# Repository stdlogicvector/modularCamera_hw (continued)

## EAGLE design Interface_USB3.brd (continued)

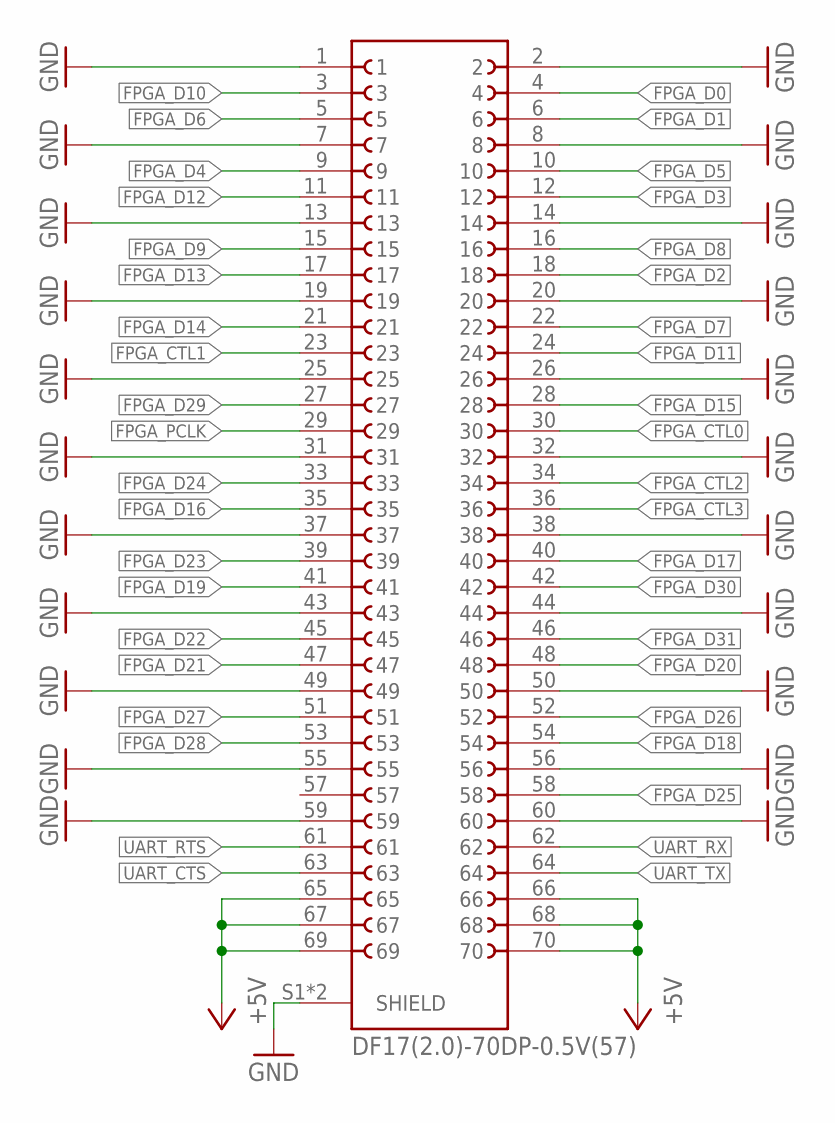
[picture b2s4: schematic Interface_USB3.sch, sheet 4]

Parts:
J1: DF17(2.0)-70DP-0.5V(57)

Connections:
+5V: J1.65, J1.66, J1.67, J1.68, J1.69, J1.70; also elsewhere on the board
FPGA_CTL0: J1.30; also elsewhere on the board
FPGA_CTL1: J1.23; also elsewhere on the board
FPGA_CTL2: J1.34; also elsewhere on the board
FPGA_CTL3: J1.36; also elsewhere on the board
FPGA_D0: J1.4; also elsewhere on the board
FPGA_D1: J1.6; also elsewhere on the board
FPGA_D2: J1.18; also elsewhere on the board
FPGA_D3: J1.12; also elsewhere on the board
FPGA_D4: J1.9; also elsewhere on the board
FPGA_D5: J1.10; also elsewhere on the board
FPGA_D6: J1.5; also elsewhere on the board
FPGA_D7: J1.22; also elsewhere on the board
FPGA_D8: J1.16; also elsewhere on the board
FPGA_D9: J1.15; also elsewhere on the board
FPGA_D10: J1.3; also elsewhere on the board
FPGA_D11: J1.24; also elsewhere on the board
FPGA_D12: J1.11; also elsewhere on the board
FPGA_D13: J1.17; also elsewhere on the board
FPGA_D14: J1.21; also elsewhere on the board
FPGA_D15: J1.28; also elsewhere on the board
FPGA_D16: J1.35; also elsewhere on the board
FPGA_D17: J1.40; also elsewhere on the board
FPGA_D18: J1.54; also elsewhere on the board
FPGA_D19: J1.41; also elsewhere on the board
FPGA_D20: J1.48; also elsewhere on the board
FPGA_D21: J1.47; also elsewhere on the board
FPGA_D22: J1.45; also elsewhere on the board
FPGA_D23: J1.39; also elsewhere on the board
FPGA_D24: J1.33; also elsewhere on the board
FPGA_D25: J1.58; also elsewhere on the board
FPGA_D26: J1.52; also elsewhere on the board
FPGA_D27: J1.51; also elsewhere on the board
FPGA_D28: J1.53; also elsewhere on the board
FPGA_D29: J1.27; also elsewhere on the board
FPGA_D30: J1.42; also elsewhere on the board
FPGA_D31: J1.46; also elsewhere on the board
FPGA_PCLK: J1.29; also elsewhere on the board
GND: J1.1, J1.2, J1.7, J1.8, J1.13, J1.14, J1.19, J1.20, J1.25, J1.26, J1.31, J1.32, J1.37, J1.38, J1.43, J1.44, J1.49, J1.50, J1.55, J1.56, J1.59, J1.60, J1.S1 (SHIELD), J1.S2 (SHIELD); also elsewhere on the board
UART_CTS: J1.63; also elsewhere on the board
UART_RTS: J1.61; also elsewhere on the board
UART_RX: J1.62; also elsewhere on the board
UART_TX: J1.64; also elsewhere on the board

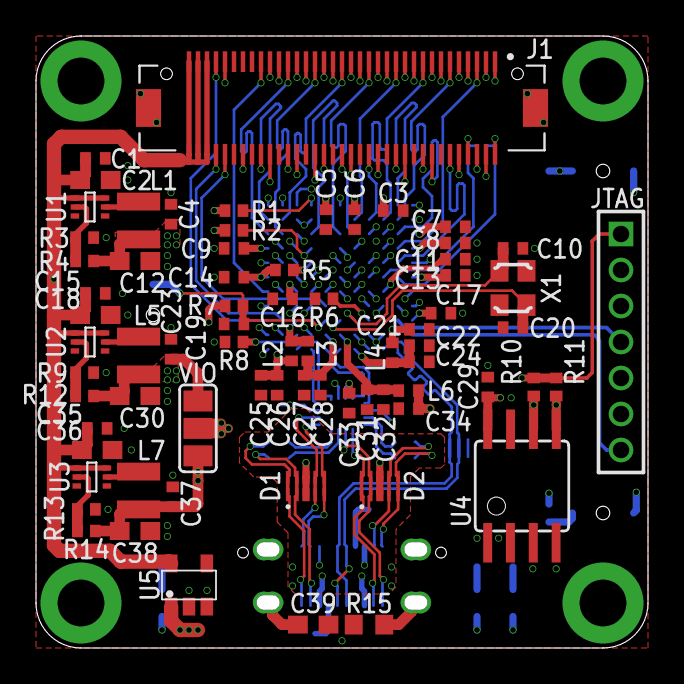
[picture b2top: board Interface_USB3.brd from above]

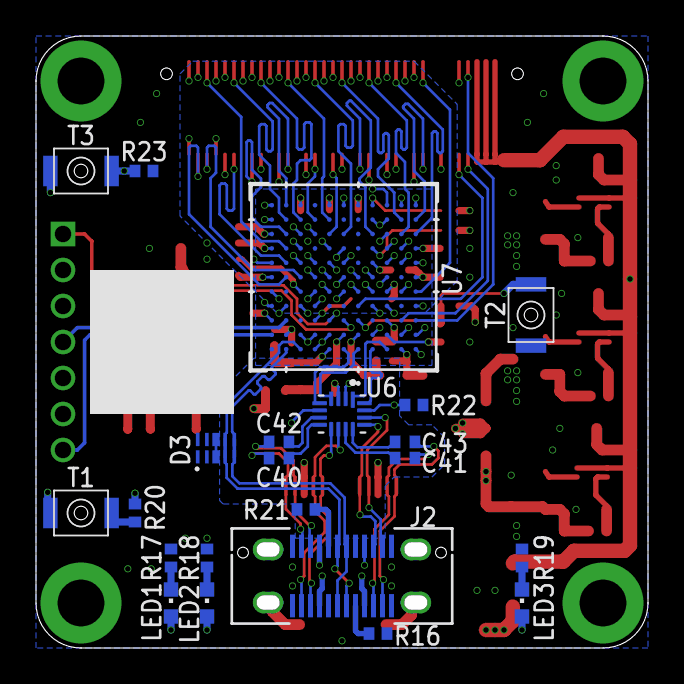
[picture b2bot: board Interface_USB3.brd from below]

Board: 6 copper layers, 34.0 x 34.0 mm, 94 parts (22 on the bottom side), 104 nets.

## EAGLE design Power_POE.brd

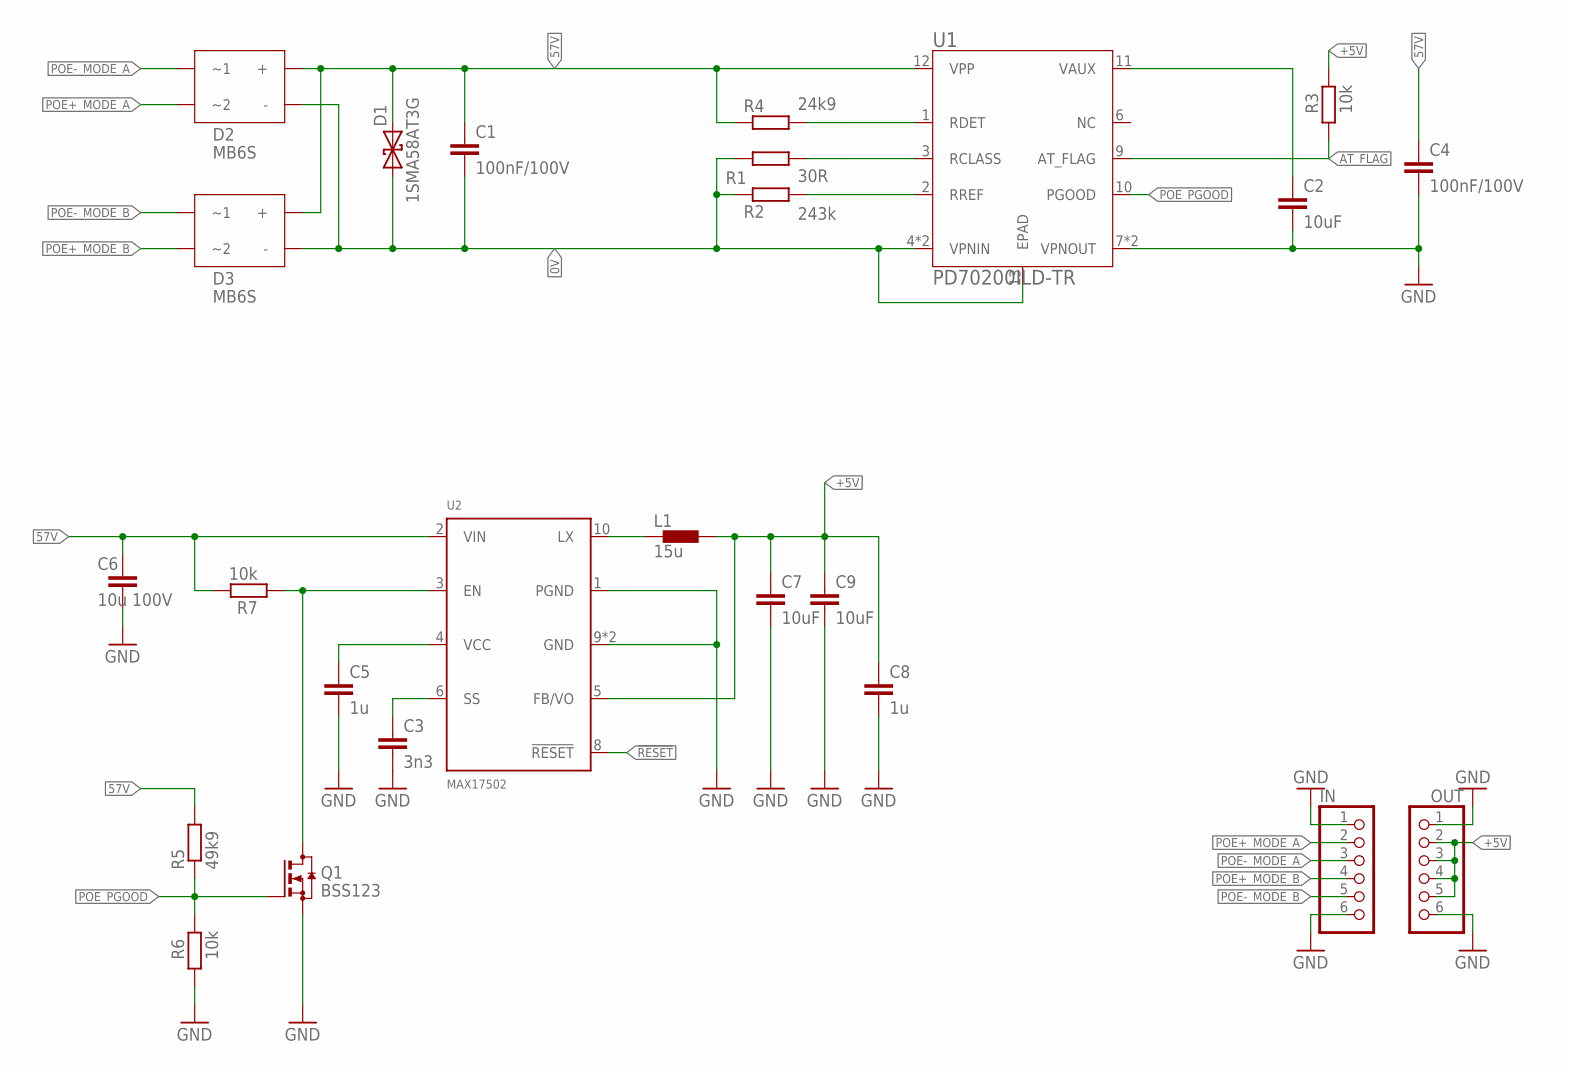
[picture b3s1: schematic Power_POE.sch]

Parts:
C1, C4: 100nF/100V; C0603; DIGIKEY 1276-6807-1-ND
C2, C7, C9: 10uF; C0805; LCSC C3039694
C3: 3n3; C0603; LCSC C1613
C5, C8: 1u; C0805; LCSC C116352
C6: 10u 100V; C1210K; DIGIKEY 1276-CL32Y106KCVZNWECT-ND
D1: 1SMA58AT3G; DO214AC; MPN SMAJ58A; DIGIKEY SMAJ58ALFCT-ND
D2, D3: MB6S; SOIC4W; LCSC C83867
IN: PINHD-1X06_2.00; 1X06M
L1: 15u; LPS6235; MPN LPS6235-153MRC; DIGIKEY 4652-LPS6235-153MRC-ND
OUT: PINHD-1X06_2.00; 1X06M
Q1: BSS123; SOT23; DIGIKEY 1727-4246-1-ND
R1: 30R; R0603; DIGIKEY 738-RMCF0603FT30R0CT-ND
R2: 243k; R0603; DIGIKEY RMCF0603FT243KCT-ND
R3, R6, R7: 10k; R0603; LCSC C25804
R4: 24k9; R0603; FARNELL 2447309
R5: 49k9; R0603; DIGIKEY RMCF0603FT49K9CT-ND
U1: PD70200ILD-TR; DFN12_4X3_MIS; LCSC C3187754
U2: MAX17502; TDFN10-3X2MM; MPN MAX17502EATB+T; DIGIKEY MAX17502EATB+TCT-ND

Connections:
0V: C1.2, D1.A (1), D2.P$2 (-), D3.P$2 (-), R1.1, R2.1, U1.4 (VPNIN), U1.5 (VPNIN), U1.13 (EPAD)
57V: C1.1, C4.1, C6.1, D1.C (2), D2.P$1 (+), D3.P$1 (+), R4.1, R5.2, R7.2, U1.12 (VPP), U2.2 (VIN)
!RESET: U2.8 (!RESET)
+5V: C7.1, C8.1, C9.1, L1.2, OUT.2, OUT.3, OUT.4, OUT.5, R3.2, U2.5 (FB/VO)
AT_FLAG: R3.1, U1.9 (AT_FLAG)
GND: C2.2, C3.2, C4.2, C5.2, C6.2, C7.2, C8.2, C9.2, IN.1, IN.6, OUT.1, OUT.6, Q1.2 (S), R6.1, U1.7 (VPNOUT), U1.8 (VPNOUT), U2.1 (PGND), U2.9 (GND), U2.TH (GND)
unnamed: R4.2, U1.1 (RDET)
unnamed: R1.2, U1.3 (RCLASS)
unnamed: C5.1, U2.4 (VCC)
unnamed: L1.1, U2.10 (LX)
unnamed: R2.2, U1.2 (RREF)
unnamed: C2.1, U1.11 (VAUX)
unnamed: Q1.3 (D), R7.1, U2.3 (EN)
unnamed: C3.1, U2.6 (SS)
POE+_MODE_A: D2.P$4 (~2), IN.2
POE+_MODE_B: D3.P$4 (~2), IN.4
POE-_MODE_A: D2.P$3 (~1), IN.3
POE-_MODE_B: D3.P$3 (~1), IN.5
POE_PGOOD: Q1.1 (G), R5.1, R6.2, U1.10 (PGOOD)

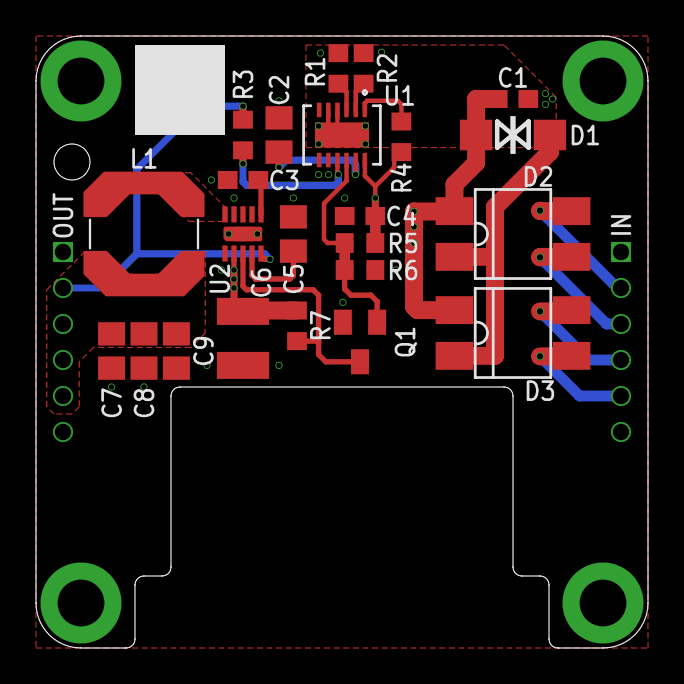
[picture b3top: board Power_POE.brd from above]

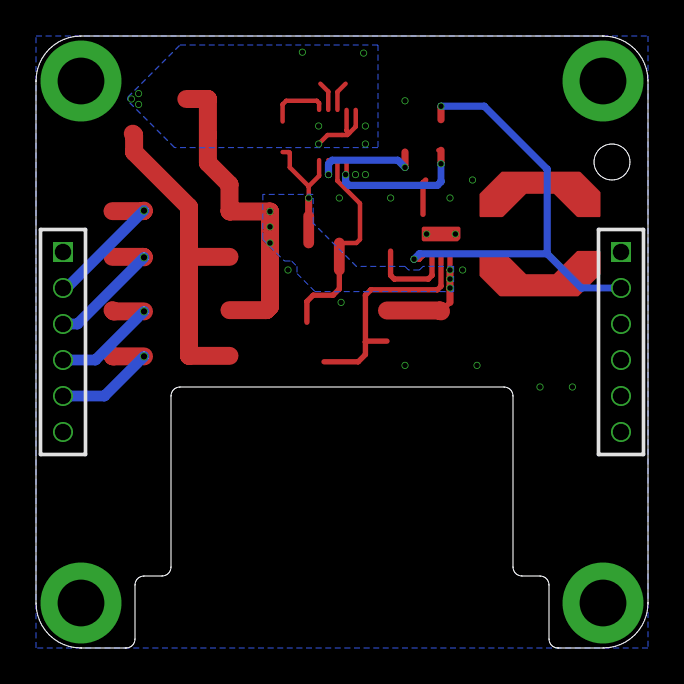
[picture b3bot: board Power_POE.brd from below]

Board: 4 copper layers, 34.0 x 34.0 mm, 25 parts (2 on the bottom side), 18 nets.

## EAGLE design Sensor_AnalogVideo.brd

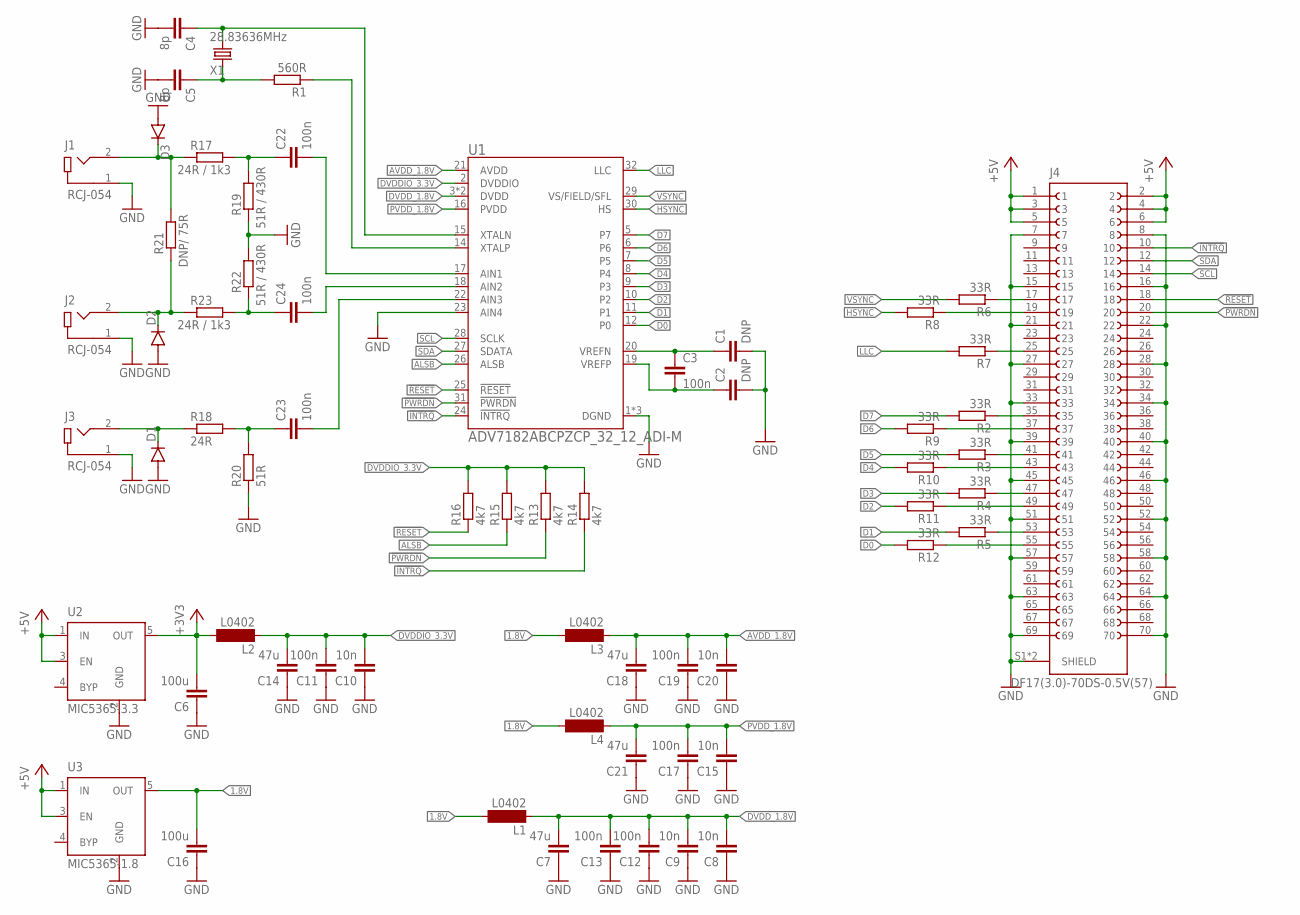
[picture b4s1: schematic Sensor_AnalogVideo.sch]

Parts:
C1, C2: DNP; C0402
C3, C11, C12, C13, C17, C19, C22, C23, C24: 100n; C0402; LCSC C1525
C4, C5: 8p; C0402; LCSC C281765
C6, C16: 100u; C1206; DIGIKEY 490-GRM31CD80J107MEA8LCT-ND
C7, C14, C18, C21: 47u; C0805; LCSC C77072
C8, C9, C10, C15, C20: 10n; C0402; LCSC C15195
D1, D2, D3: DIODE-SOD323-W; SOD323-W
J1, J2, J3: RCJ-054; CUI_RCJ-054; DIGIKEY CP-1427-ND
J4: DF17(3.0)-70DS-0.5V(57)
L1, L2, L3, L4: L0402; C0402; LCSC C88970
R1: 560R; R0402
R2, R3, R4, R5, R6, R7, R8, R9, R10, R11, R12: 33R; R0402
R13, R14, R15, R16: 4k7; R0402; LCSC C25900
R17, R23: 24R / 1k3; R0603
R18: 24R; R0603
R19, R22: 51R / 430R; R0603
R20: 51R; R0603
R21: DNP/ 75R; R0603
U1: ADV7182ABCPZCP_32_12_ADI-M; CP_32_12_ADI-M; DIGIKEY 505-ADV7182ABCPZ-ND
U2: MIC5365-3.3; SOT23-5; DIGIKEY 576-4085-1-ND
U3: MIC5365-1.8; SOT23-5; DIGIKEY 576-4082-1-ND
X1: 28.83636MHz; 2520; DIGIKEY XC3048CT-ND

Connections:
1.8V: C16.1, L1.2, L3.2, L4.2, U3.5 (OUT)
!INTRQ: J4.10, R14.1, U1.24 (!INTRQ)
!PWRDN: J4.20, R13.1, U1.31 (!PWRDN)
!RESET: J4.18, R16.1, U1.25 (!RESET)
+3V3: C6.1, L2.2, U2.5 (OUT)
+5V: J4.1, J4.2, J4.3, J4.4, J4.5, J4.6, U2.1 (IN), U2.3 (EN), U3.1 (IN), U3.3 (EN)
ALSB: R15.1, U1.26 (ALSB)
AVDD_1.8V: C18.2, C19.2, C20.2, L3.1, U1.21 (AVDD)
D0: R12.2, U1.12 (P0)
D1: R5.2, U1.11 (P1)
D2: R11.2, U1.10 (P2)
D3: R4.2, U1.9 (P3)
D4: R10.2, U1.8 (P4)
D5: R3.2, U1.7 (P5)
D6: R9.2, U1.6
D7: R2.2, U1.5 (P7)
DVDDIO_3.3V: C10.2, C11.2, C14.2, L2.1, R13.2, R14.2, R15.2, R16.2, U1.2 (DVDDIO)
DVDD_1.8V: C7.2, C8.2, C9.2, C12.2, C13.2, L1.1, U1.3 (DVDD), U1.13 (DVDD)
GND: C1.2, C2.2, C4.2, C5.2, C6.2, C7.1, C8.1, C9.1, C10.1, C11.1, C12.1, C13.1, C14.1, C15.1, C16.2, C17.1, C18.1, C19.1, C20.1, C21.1, D1.A, D2.A, D3.A, J1.1, J2.1, J3.1, J4.7, J4.8, J4.15, J4.16, J4.21, J4.22, J4.27, J4.28, J4.33, J4.34, J4.39, J4.40, J4.45, J4.46, J4.51, J4.52, J4.57, J4.58, J4.63, J4.64, J4.69, J4.70, J4.S1 (SHIELD), J4.S2 (SHIELD), R19.1, R20.1, R22.2, U1.1 (DGND), U1.4 (DGND), U1.23 (AIN4), U1.33 (DGND), U2.2 (GND), U3.2 (GND)
HSYNC: R8.2, U1.30 (HS)
LLC: R7.2, U1.32 (LLC)
unnamed: C1.1, C3.1, U1.20 (VREFN)
unnamed: C2.1, C3.2, U1.19 (VREFP)
unnamed: D3.C, J1.2, R17.1, R21.2
unnamed: D2.C, J2.2, R21.1, R23.1
unnamed: C22.1, R17.2, R19.2
unnamed: C24.1, R22.1, R23.2
unnamed: C22.2, U1.17 (AIN1)
unnamed: C24.2, U1.18 (AIN2)
unnamed: D1.C, J3.2, R18.1
unnamed: C23.2, U1.22 (AIN3)
unnamed: C23.1, R18.2, R20.2
unnamed: J4.17, R6.1
unnamed: J4.19, R8.1
unnamed: J4.25, R7.1
unnamed: J4.35, R2.1
unnamed: J4.37, R9.1
unnamed: J4.41, R3.1
unnamed: J4.43, R10.1
unnamed: J4.47, R4.1
unnamed: J4.49, R11.1
unnamed: J4.53, R5.1
unnamed: J4.55, R12.1
unnamed: R1.1, U1.14 (XTALP)
PVDD_1.8V: C15.2, C17.2, C21.2, L4.1, U1.16 (PVDD)
SCL: J4.14, U1.28 (SCLK)
SDA: J4.12, U1.27 (SDATA)
VSYNC: R6.2, U1.29 (VS/FIELD/SFL)
XTAL_IN: C4.1, U1.15 (XTALN), X1.1
XTAL_OUT: C5.1, R1.2, X1.3 (2)

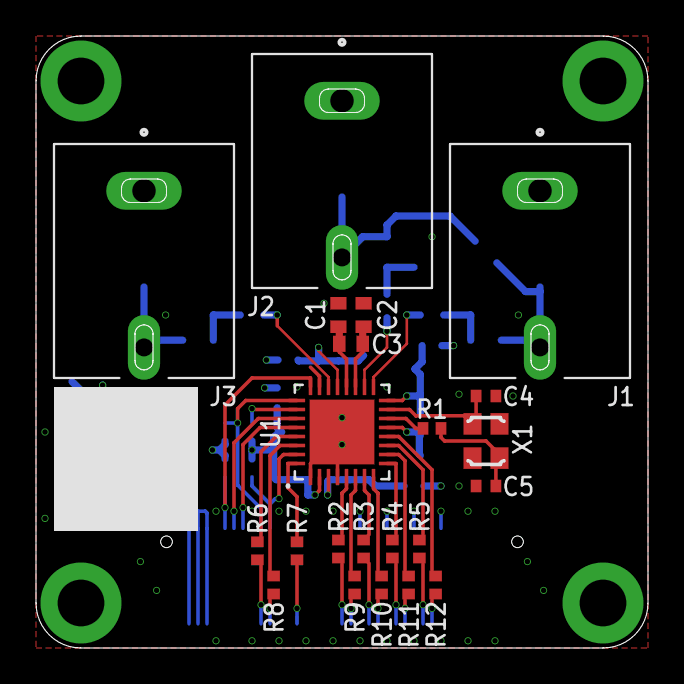
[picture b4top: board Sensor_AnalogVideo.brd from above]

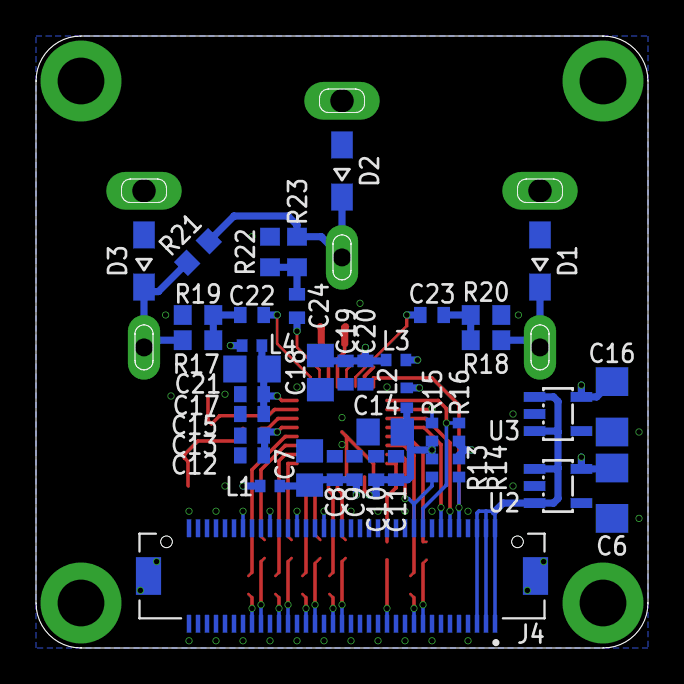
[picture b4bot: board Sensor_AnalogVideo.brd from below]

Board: 4 copper layers, 34.0 x 34.0 mm, 62 parts (40 on the bottom side), 50 nets.

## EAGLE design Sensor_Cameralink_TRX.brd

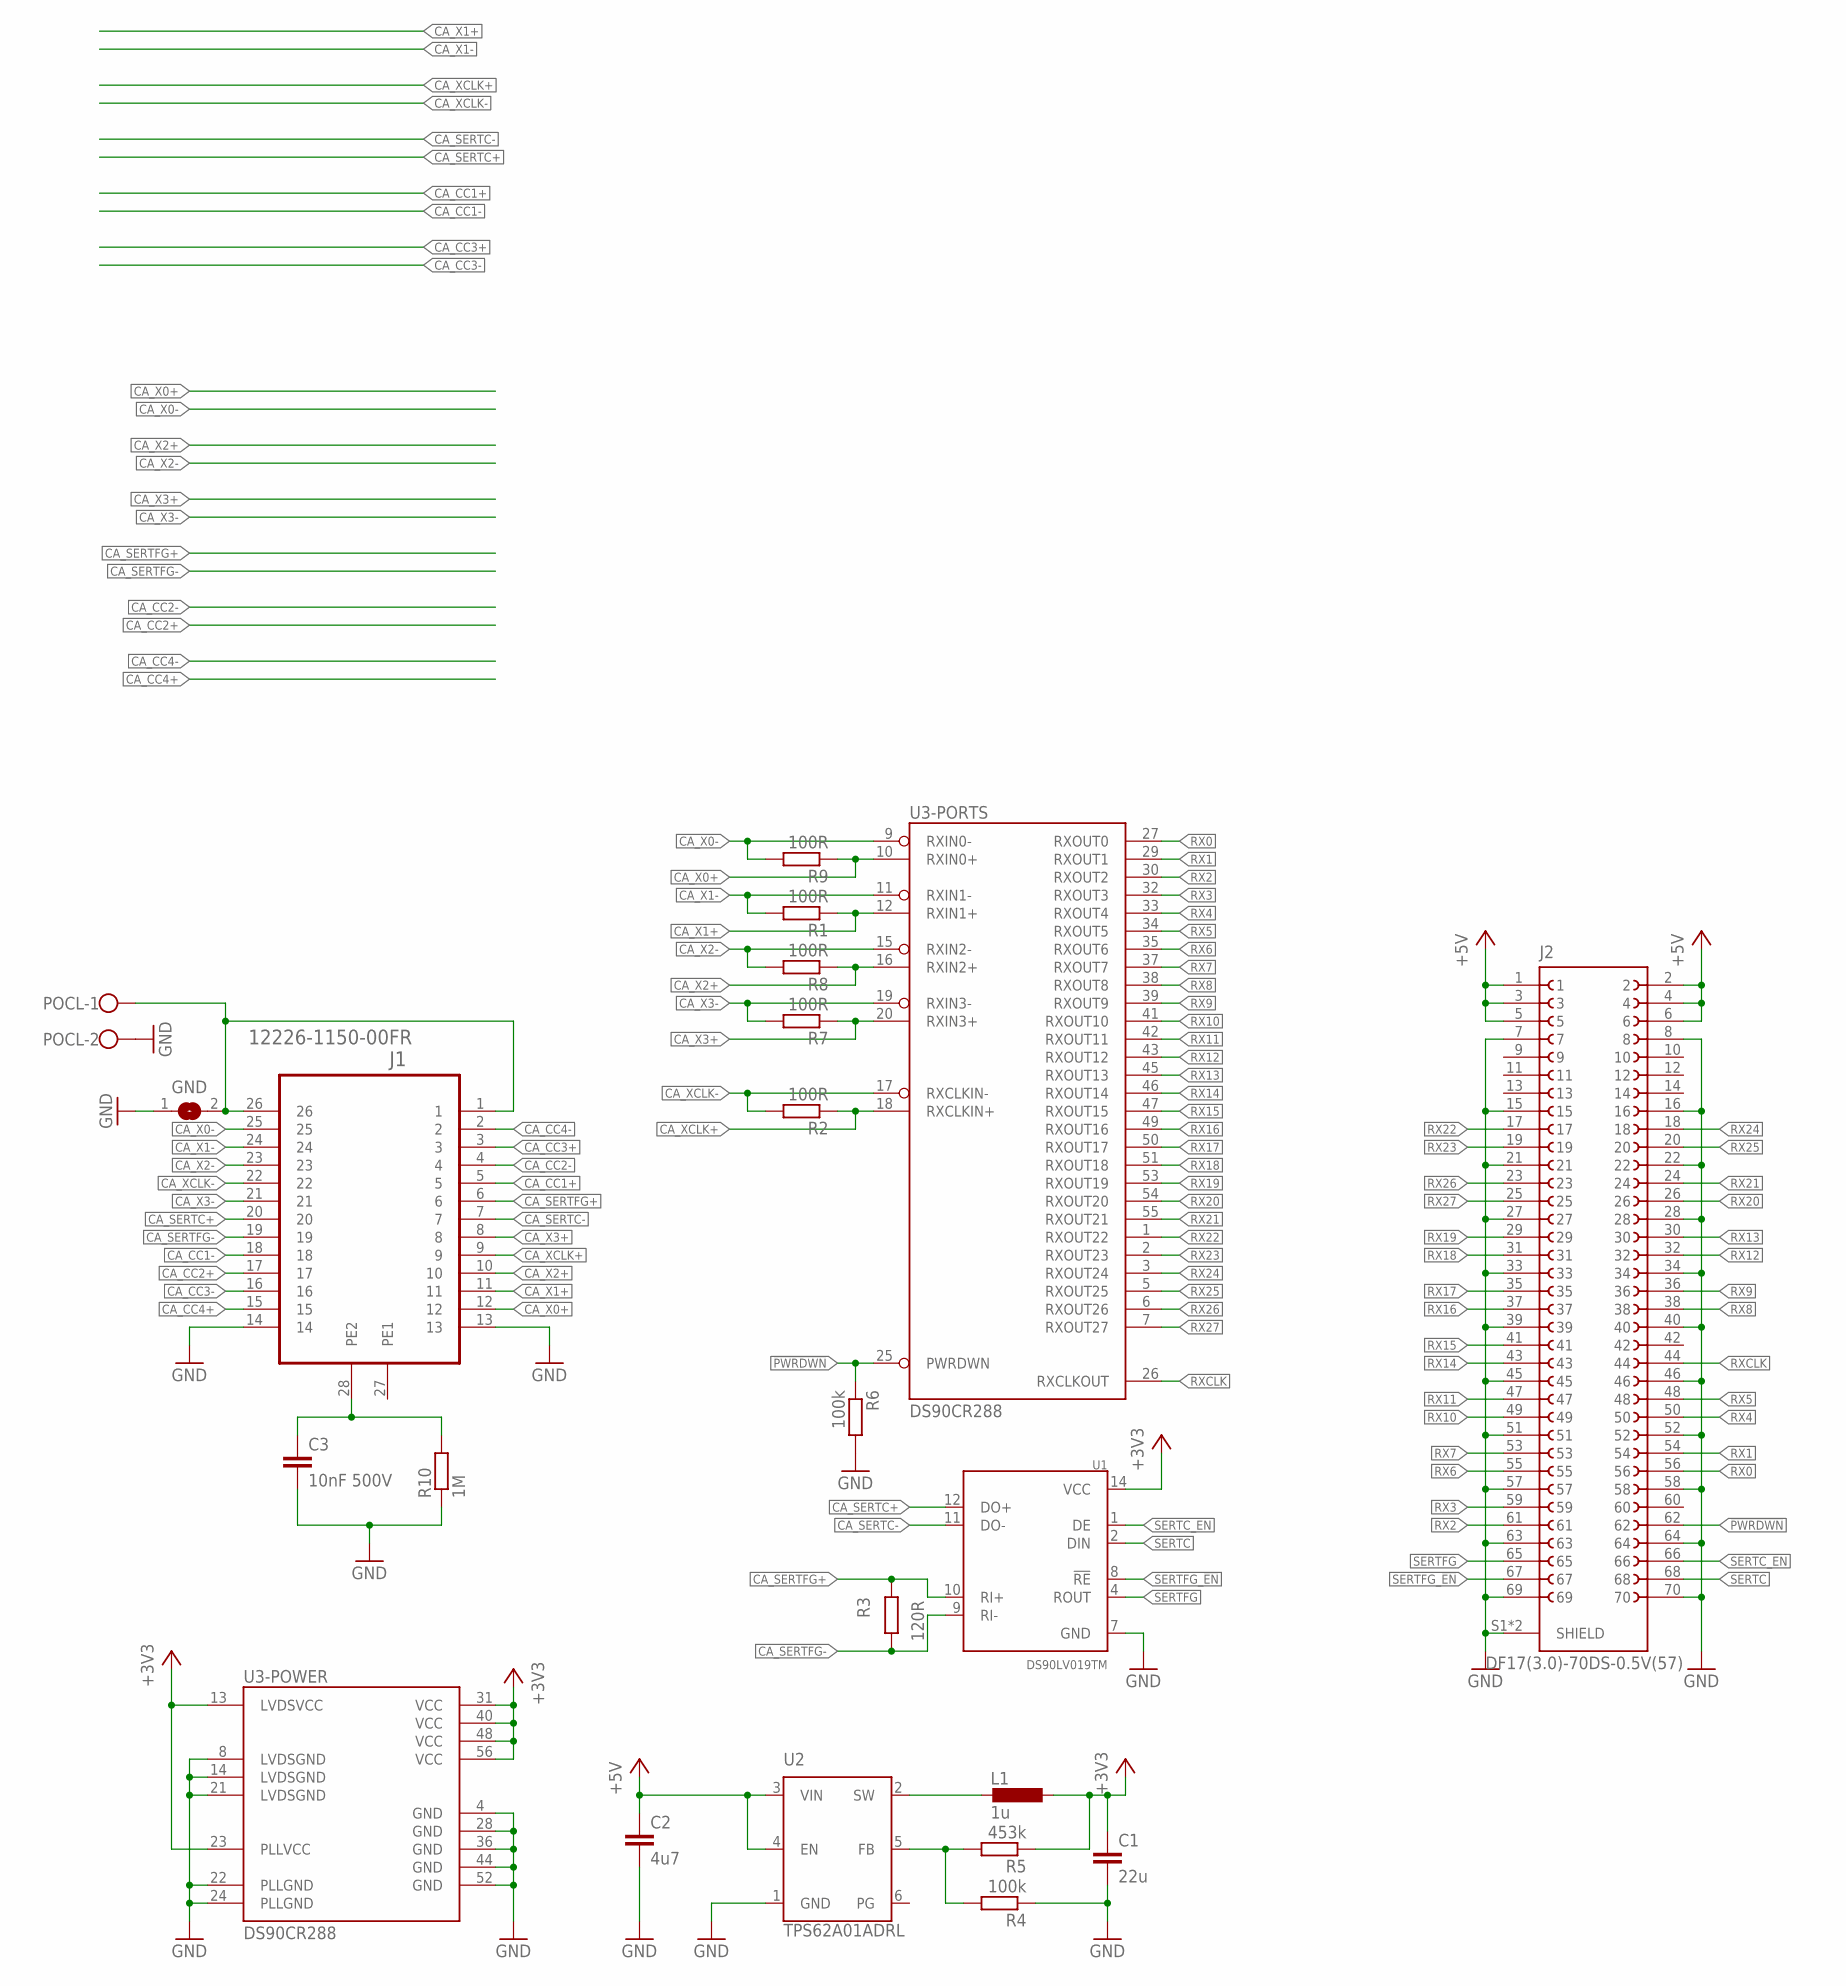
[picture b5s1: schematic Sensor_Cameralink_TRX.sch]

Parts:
C1: 22u; C0603; LCSC C109448
C2: 4u7; C0603; LCSC C19666
C3: 10nF 500V; C0805
GND: SJ
J1: 12226-1150-00FR; 3M_12226-1150-00FR
J2: DF17(3.0)-70DS-0.5V(57)
L1: 1u; L1008; MPN LQM2HPN1R0MG0L; DIGIKEY 490-5112-1-ND
POCL: W237-102
R1, R2, R7, R8, R9: 100R; R0402
R3: 120R; R0402
R4, R6: 100k; R0402; DIGIKEY RMCF0402FT100KCT-ND
R5: 453k; R0402; LCSC C137978
R10: 1M; R0805
U1: DS90LV019TM; SO-14
U2: TPS62A01ADRL; SOTFL50P160X60-6N; DIGIKEY 296-TPS62A01ADRLRCT-ND
U3: DS90CR288; HTSSOP56

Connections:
!PWRDWN: J2.62, R6.1, U3.25 (PWRDWN)
+3V3: C1.1, L1.1, R5.1, U1.14 (VCC), U3.13 (LVDSVCC), U3.23 (PLLVCC), U3.31 (VCC), U3.40 (VCC), U3.48 (VCC), U3.56 (VCC)
+5V: C2.1, J2.1, J2.2, J2.3, J2.4, J2.5, J2.6, U2.3 (VIN), U2.4 (EN)
CA_CC1+: J1.5
CA_CC1-: J1.18
CA_CC2+: J1.17
CA_CC2-: J1.4
CA_CC3+: J1.3
CA_CC3-: J1.16
CA_CC4+: J1.15
CA_CC4-: J1.2
CA_SERTC+: J1.20, U1.12 (DO+)
CA_SERTC-: J1.7, U1.11 (DO-)
CA_SERTFG+: J1.6, R3.1, U1.10 (RI+)
CA_SERTFG-: J1.19, R3.2, U1.9 (RI-)
CA_X0+: J1.12, R9.1, U3.10 (RXIN0+)
CA_X0-: J1.25, R9.2, U3.9 (RXIN0-)
CA_X1+: J1.11, R1.1, U3.12 (RXIN1+)
CA_X1-: J1.24, R1.2, U3.11 (RXIN1-)
CA_X2+: J1.10, R8.1, U3.16 (RXIN2+)
CA_X2-: J1.23, R8.2, U3.15 (RXIN2-)
CA_X3+: J1.8, R7.1, U3.20 (RXIN3+)
CA_X3-: J1.21, R7.2, U3.19 (RXIN3-)
CA_XCLK+: J1.9, R2.1, U3.18 (RXCLKIN+)
CA_XCLK-: J1.22, R2.2, U3.17 (RXCLKIN-)
GND: C1.2, C2.2, C3.2, GND.1, J1.13, J1.14, J2.7, J2.8, J2.15, J2.16, J2.21, J2.22, J2.27, J2.28, J2.33, J2.34, J2.39, J2.40, J2.45, J2.46, J2.51, J2.52, J2.57, J2.58, J2.63, J2.64, J2.69, J2.70, J2.S1 (SHIELD), J2.S2 (SHIELD), POCL.2, R4.1, R6.2, R10.1, U1.7 (GND), U2.1 (GND), U3.4 (GND), U3.8 (LVDSGND), U3.14 (LVDSGND), U3.21 (LVDSGND), U3.22 (PLLGND), U3.24 (PLLGND), U3.28 (GND), U3.36 (GND), U3.44 (GND), U3.52 (GND)
unnamed: C3.1, J1.28 (PE2), R10.2
unnamed: GND.2, J1.1, J1.26, POCL.1
unnamed: R4.2, R5.2, U2.5 (FB)
unnamed: L1.2, U2.2 (SW)
RX0: J2.56, U3.27 (RXOUT0)
RX1: J2.54, U3.29 (RXOUT1)
RX2: J2.61, U3.30 (RXOUT2)
RX3: J2.59, U3.32 (RXOUT3)
RX4: J2.50, U3.33 (RXOUT4)
RX5: J2.48, U3.34 (RXOUT5)
RX6: J2.55, U3.35 (RXOUT6)
RX7: J2.53, U3.37 (RXOUT7)
RX8: J2.38, U3.38 (RXOUT8)
RX9: J2.36, U3.39 (RXOUT9)
RX10: J2.49, U3.41 (RXOUT10)
RX11: J2.47, U3.42 (RXOUT11)
RX12: J2.32, U3.43 (RXOUT12)
RX13: J2.30, U3.45 (RXOUT13)
RX14: J2.43, U3.46 (RXOUT14)
RX15: J2.41, U3.47 (RXOUT15)
RX16: J2.37, U3.49 (RXOUT16)
RX17: J2.35, U3.50 (RXOUT17)
RX18: J2.31, U3.51 (RXOUT18)
RX19: J2.29, U3.53 (RXOUT19)
RX20: J2.26, U3.54 (RXOUT20)
RX21: J2.24, U3.55 (RXOUT21)
RX22: J2.17, U3.1 (RXOUT22)
RX23: J2.19, U3.2 (RXOUT23)
RX24: J2.18, U3.3 (RXOUT24)
RX25: J2.20, U3.5 (RXOUT25)
RX26: J2.23, U3.6 (RXOUT26)
RX27: J2.25, U3.7 (RXOUT27)
RXCLK: J2.44, U3.26 (RXCLKOUT)
SERTC: J2.68, U1.2 (DIN)
SERTC_EN: J2.66, U1.1 (DE)
SERTFG: J2.65, U1.4 (ROUT)
SERTFG_!EN: J2.67, U1.8 (!RE)

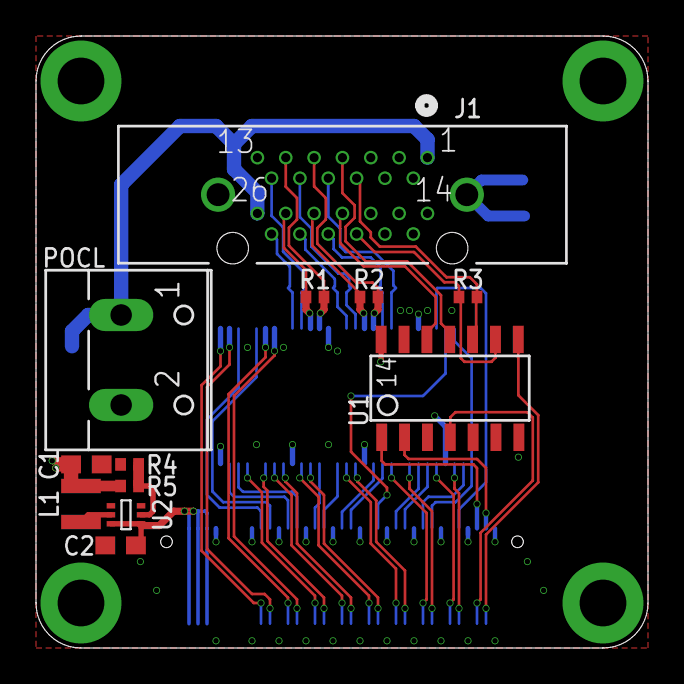
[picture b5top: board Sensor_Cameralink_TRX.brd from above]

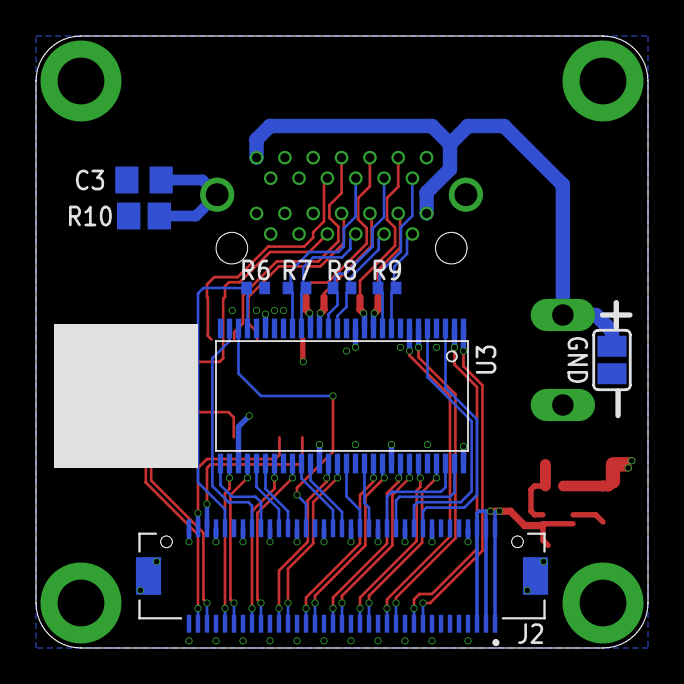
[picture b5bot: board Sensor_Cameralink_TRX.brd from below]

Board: 4 copper layers, 34.0 x 34.0 mm, 21 parts (9 on the bottom side), 55 nets.

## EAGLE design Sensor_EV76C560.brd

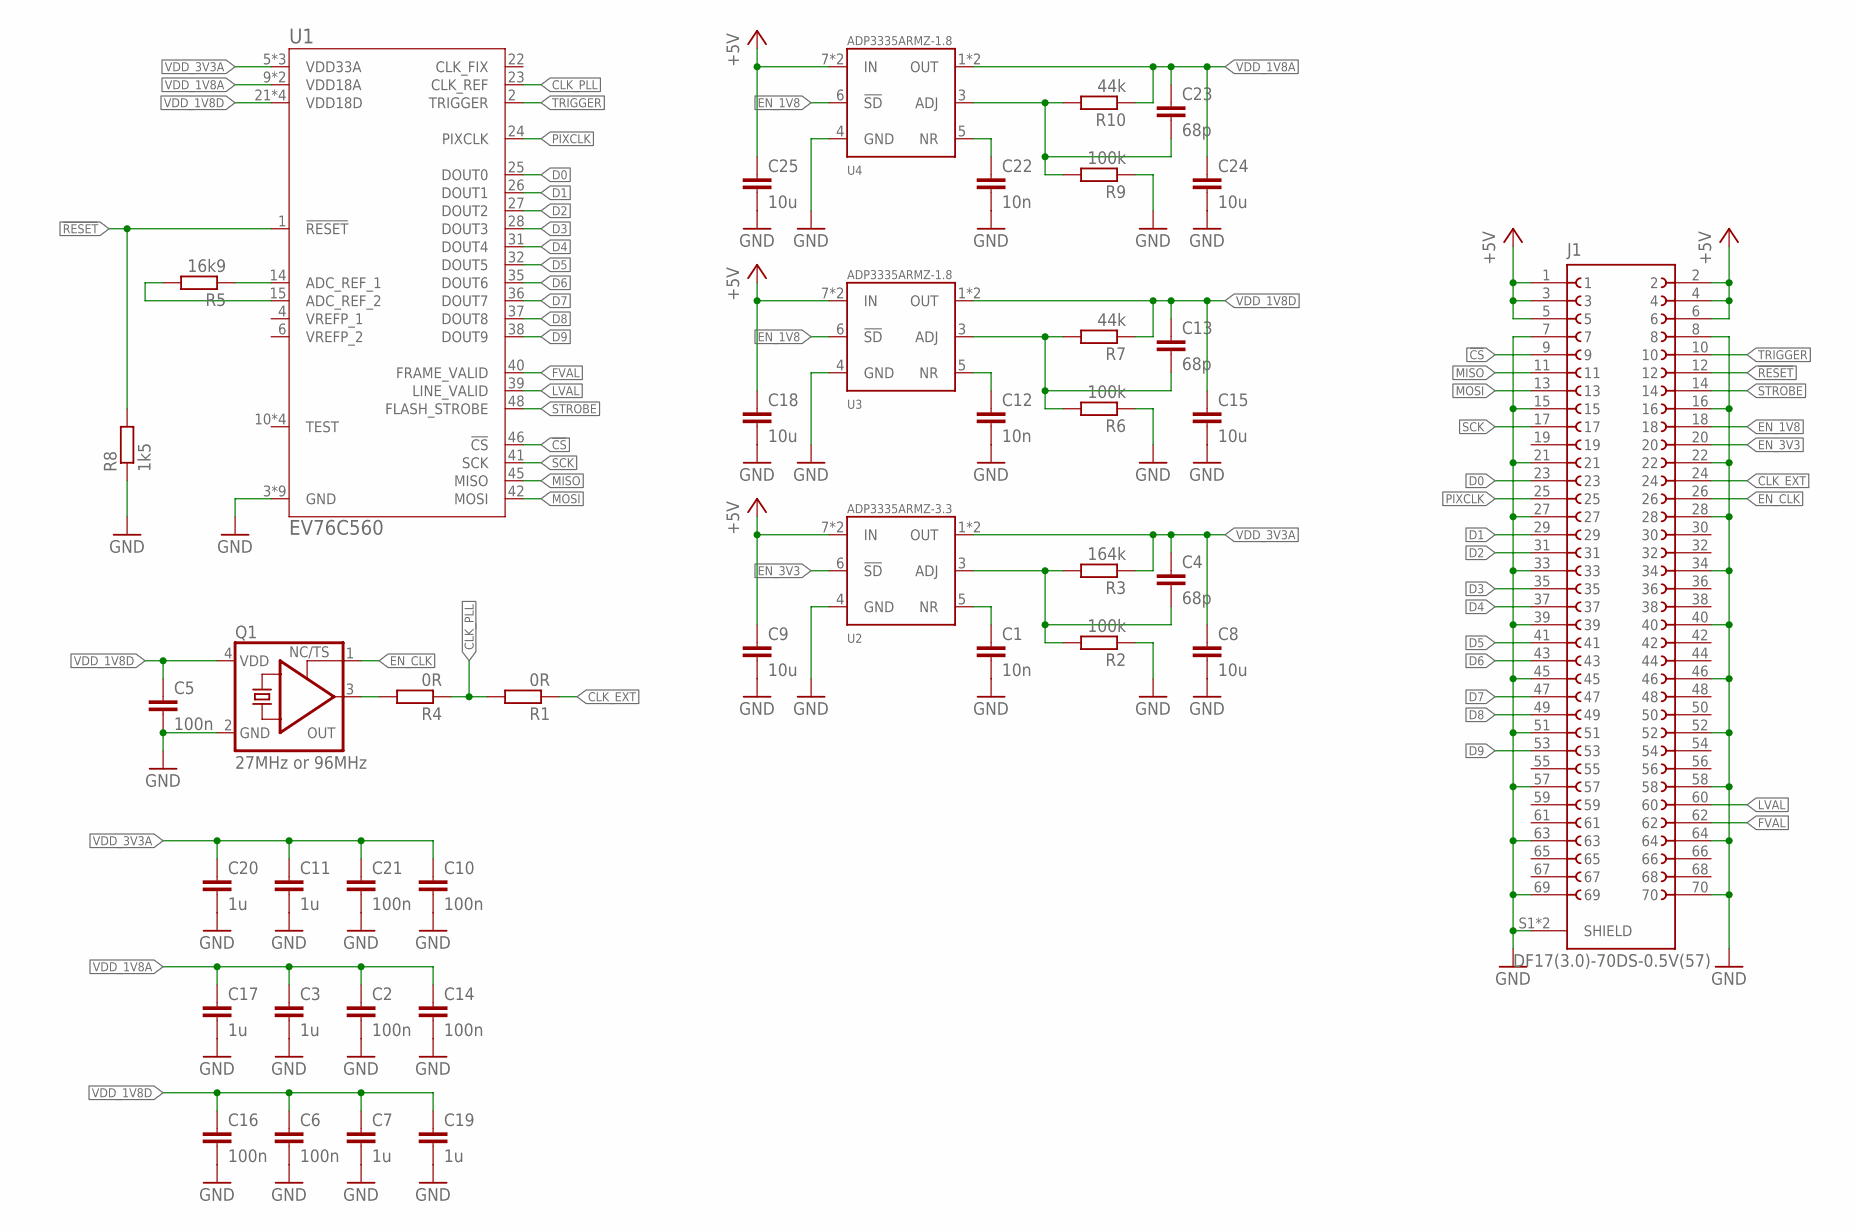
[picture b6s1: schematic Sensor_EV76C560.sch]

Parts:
C1, C12, C22: 10n; C0402; LCSC C1525
C2, C5, C6, C10, C14, C16, C21: 100n; C0402; LCSC C1525
C3, C7, C11, C17, C19, C20: 1u; C0402
C4, C13, C23: 68p; C0402; LCSC C1525
C8, C9, C15, C18, C24, C25: 10u; C0603
J1: DF17(3.0)-70DS-0.5V(57)
Q1: 27MHz or 96MHz; 3.2X2.5_KXO-V96
R1, R4: 0R; R0402
R2, R6, R9: 100k; R0402
R3: 164k; R0402
R5: 16k9; R0402
R7, R10: 44k; R0402
R8: 1k5; R0402
U1: EV76C560; LCC-48
U2: ADP3335ARMZ-3.3; MSOP08; DIGIKEY 505-ADP3335ARMZ-3.3RL7CT-ND
U3: ADP3335ARMZ-1.8; MSOP08; DIGIKEY 505-ADP3335ARMZ-2.5-RLCT-ND
U4: ADP3335ARMZ-1.8; MSOP08; DIGIKEY 505-ADP3335ARMZ-1.8-R7CT-ND

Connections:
!CS: J1.9, U1.46 (!CS)
!RESET: J1.12, R8.2, U1.1 (!RESET)
+5V: C9.1, C18.1, C25.1, J1.1, J1.2, J1.3, J1.4, J1.5, J1.6, U2.7 (IN), U2.8 (IN), U3.7 (IN), U3.8 (IN), U4.7 (IN), U4.8 (IN)
CLK: Q1.3 (OUT), R4.2
CLK_EXT: J1.24, R1.1
CLK_PLL: R1.2, R4.1, U1.23 (CLK_REF)
D0: J1.23, U1.25 (DOUT0)
D1: J1.29, U1.26 (DOUT1)
D2: J1.31, U1.27 (DOUT2)
D3: J1.35, U1.28 (DOUT3)
D4: J1.37, U1.31 (DOUT4)
D5: J1.41, U1.32 (DOUT5)
D6: J1.43, U1.35 (DOUT6)
D7: J1.47, U1.36 (DOUT7)
D8: J1.49, U1.37 (DOUT8)
D9: J1.53, U1.38 (DOUT9)
EN_1V8: J1.18, U3.6 (!SD), U4.6 (!SD)
EN_3V3: J1.20, U2.6 (!SD)
EN_CLK: J1.26, Q1.1 (TS)
FVAL: J1.62, U1.40 (FRAME_VALID)
GND: C1.2, C2.2, C3.2, C5.2, C6.2, C7.2, C8.2, C9.2, C10.2, C11.2, C12.2, C14.2, C15.2, C16.2, C17.2, C18.2, C19.2, C20.2, C21.2, C22.2, C24.2, C25.2, J1.7, J1.8, J1.15, J1.16, J1.21, J1.22, J1.27, J1.28, J1.33, J1.34, J1.39, J1.40, J1.45, J1.46, J1.51, J1.52, J1.57, J1.58, J1.63, J1.64, J1.69, J1.70, J1.S1 (SHIELD), J1.S2 (SHIELD), Q1.2 (GND), R2.1, R6.1, R8.1, R9.1, U1.3 (GND), U1.7 (GND), U1.13 (GND), U1.16 (GND), U1.19 (GND), U1.20 (GND), U1.29 (GND), U1.33 (GND), U1.43 (GND), U2.4 (GND), U3.4 (GND), U4.4 (GND)
LVAL: J1.60, U1.39 (LINE_VALID)
MISO: J1.11, U1.45 (MISO)
MOSI: J1.13, U1.42 (MOSI)
unnamed: C1.1, U2.5 (NR)
unnamed: C22.1, U4.5 (NR)
unnamed: C12.1, U3.5 (NR)
unnamed: C23.2, R9.2, R10.2, U4.3 (ADJ)
unnamed: C13.2, R6.2, R7.2, U3.3 (ADJ)
unnamed: R5.1, U1.14 (ADC_REF_1)
unnamed: R5.2, U1.15 (ADC_REF_2)
unnamed: C4.2, R2.2, R3.2, U2.3 (ADJ)
PIXCLK: J1.25, U1.24 (PIXCLK)
SCK: J1.17, U1.41 (SCK)
STROBE: J1.14, U1.48 (FLASH_STROBE)
TRIGGER: J1.10, U1.2 (TRIGGER)
VDD_1V8A: C2.1, C3.1, C14.1, C17.1, C23.1, C24.1, R10.1, U1.9 (VDD18A), U1.18 (VDD18A), U4.1 (OUT), U4.2 (OUT)
VDD_1V8D: C5.1, C6.1, C7.1, C13.1, C15.1, C16.1, C19.1, Q1.4 (VDD), R7.1, U1.21 (VDD18D), U1.30 (VDD18D), U1.34 (VDD18D), U1.44 (VDD18D), U3.1 (OUT), U3.2 (OUT)
VDD_3V3A: C4.1, C8.1, C10.1, C11.1, C20.1, C21.1, R3.1, U1.5 (VDD33A), U1.8 (VDD33A), U1.17 (VDD33A), U2.1 (OUT), U2.2 (OUT)

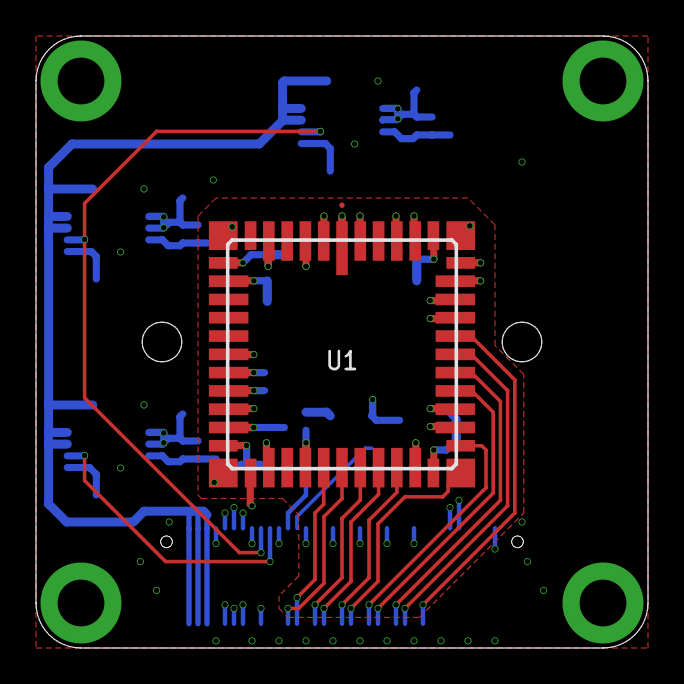
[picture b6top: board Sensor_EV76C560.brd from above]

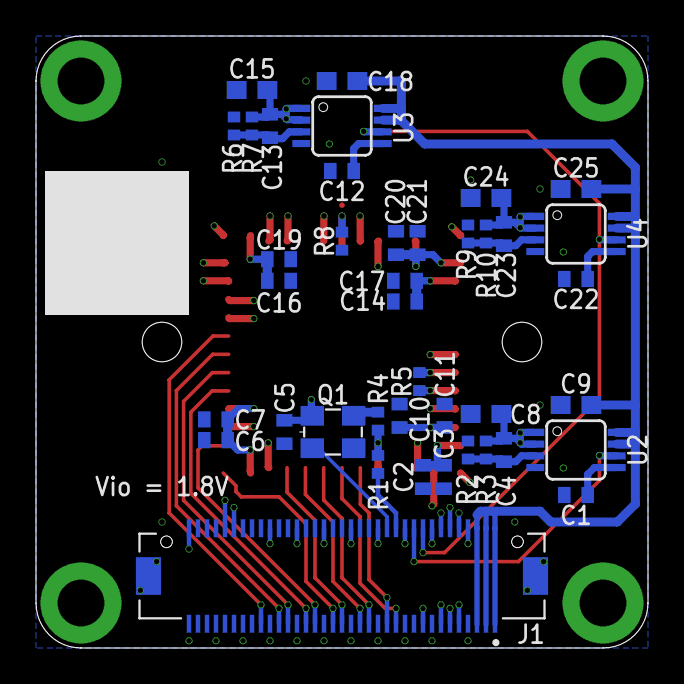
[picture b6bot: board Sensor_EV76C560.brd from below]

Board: 4 copper layers, 34.0 x 34.0 mm, 41 parts (40 on the bottom side), 39 nets.
